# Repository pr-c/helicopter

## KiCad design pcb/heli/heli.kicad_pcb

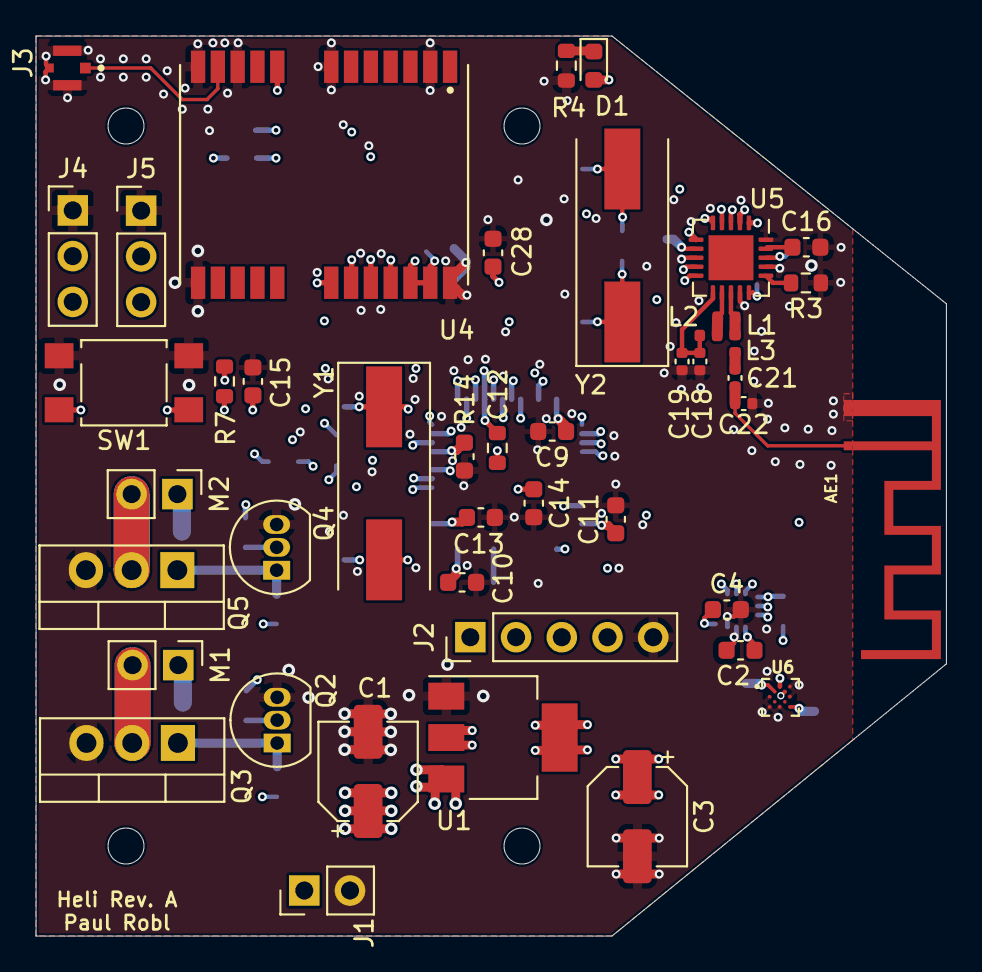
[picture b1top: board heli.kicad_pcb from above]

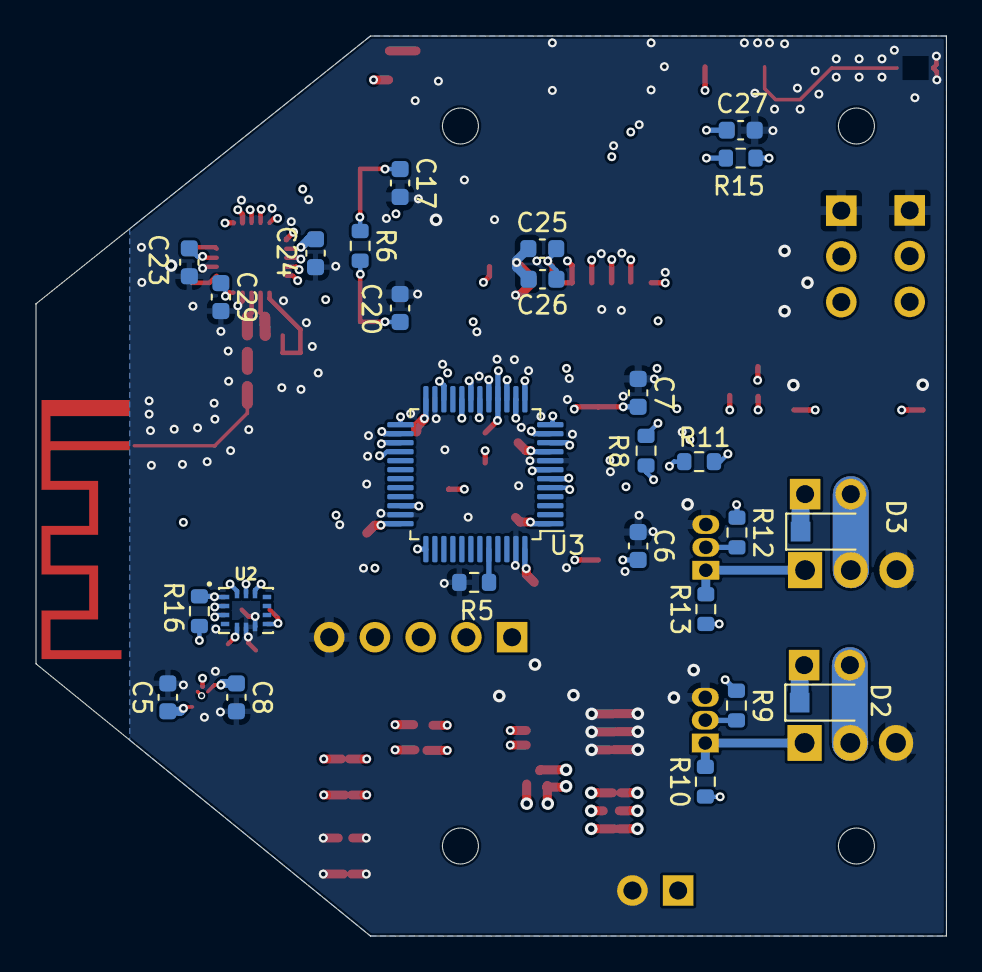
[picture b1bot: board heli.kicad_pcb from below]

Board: 4 copper layers, 50.6 x 50.0 mm, 72 parts (26 on the bottom side), 44 nets.

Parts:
**REF: MountingHole_2mm
**REF#2: MountingHole_2mm
AE1: Antenna_Shield; TRACE_ANTENNA_2.4GHZ_15.2MM
C1: 10uF; CP_Elec_5x5.4
C2, C4, C5, C8, C9, C10, C11, C12, C13, C15, C25, C26, C27, C29: 100nF; C_0603_1608Metric
C3: 22uF; CP_Elec_5x5.4
C6, C7, C17, C20: 30pF; C_0603_1608Metric
C14, C28: 10uF; C_0603_1608Metric
C16: 33nF; C_0603_1608Metric
C18: 2.2nF; C_0402_1005Metric
C19: 4.7pF; C_0402_1005Metric
C21: 1.5pF; C_0402_1005Metric
C22: 1.0pF; C_0402_1005Metric
C23: 10nF; C_0603_1608Metric
C24: 1nF; C_0603_1608Metric
D1: LED; LED_0603_1608Metric
D2, D3: 1N5819; D_SOD-123F
J1: Batterie; PinHeader_1x02_P2.54mm_Vertical
J2: Debug; PinHeader_1x05_P2.54mm_Vertical
J3: CONMHF4-SMD-G-T; LINX_CONMHF4-SMD-G-T
J4, J5: Servo; PinHeader_1x03_P2.54mm_Vertical
L1: 8.2nH; L_0402_1005Metric
L2: 2.7nH; L_0402_1005Metric
L3: 3.9nH; L_0402_1005Metric
M1, M2: Motor_DC; PinHeader_1x02_P2.54mm_Vertical
Q2, Q4: BC547; TO-92_Inline
Q3, Q5: IRLZ44N; TO-220-3_Vertical
R3: 22k; R_0603_1608Metric
R4: 70; R_0603_1608Metric
R5, R7, R10, R13, R15: 10k; R_0603_1608Metric
R6, R8, R11, R14, R16: 1M; R_0603_1608Metric
R9, R12: 20k; R_0603_1608Metric
SW1: SW_MEC_5E; SW_SPST_TL3305A
U1: AZ1117-3.3; SOT-223-3_TabPin2
U2: BMI270; XDCR_BMI270
U3: STM32F103CBTx; LQFP-48_7x7mm_P0.5mm
U4: NEO-M9N-00B; XCVR_NEO-M9N-00B
U5: NRF24L01; QFN-20-1EP_4x4mm_P0.5mm_EP2.5x2.5mm
U6: BMM150; XDCR_BMM150
Y1: 8MHz; Crystal_SMD_HC49-SD
Y2: 16MHz; Crystal_SMD_HC49-SD

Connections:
3.3V: C2.1, C3.1, C4.1, C5.1, C8.1, C9.1, C10.1, C11.1, C12.1, C13.1, C14.1, C23.1, C24.1, C25.1, C26.1, C28.1, C29.1, D1.2 (A), J2.1, J4.2, J5.2, R7.1, R8.1, R11.1, R14.1, R15.1, R16.1, U1.2 (VO), U2.5 (VDDIO), U2.8 (VDD), U3.1 (VBAT), U3.9 (VDDA), U3.24 (VDD), U3.36 (VDD), U3.48 (VDD), U4.22 (V_BCKP), U4.23 (VCC), U5.7 (VDD), U5.15 (VDD), U5.18 (VDD), U6.A1 (PS), U6.B2 (VDDIO), U6.E5 (VDD)
7.4V: C1.1, D2.1 (K), D3.1 (K), J1.1, M1.1 (+), M2.1 (+), R10.1, R13.1, U1.3 (VI)
/Back Motor/M-: D3.2 (A), M2.2 (-), Q5.2 (D)
/GPS/GPS50ohms: J3.1, U4.11 (RF_IN)
/IMU/SCL: U2.3 (ASCX), U6.A3 (SCK)
/IMU/SDA: U2.2 (ASDX), U6.B4 (SDI)
/Main Motor/M-: D2.2 (A), M1.2 (-), Q3.2 (D)
/PWM1: R8.2, R9.1, U3.10 (PA0)
/PWM2: R11.2, R12.1, U3.11 (PA1)
/Radio/RADIO50ohm: AE1.1 (A), C21.2, C22.2
/SERVO1: J4.3, U3.12 (PA2)
/SERVO2: J5.3, U3.13 (PA3)
GND: AE1.2 (Shield), C1.2, C2.2, C3.2, C4.2, C5.2, C6.1, C7.1, C8.2, C9.2, C10.2, C11.2, C12.2, C13.2, C14.2, C15.1, C16.2, C17.2, C18.1, C19.1, C20.2, C22.1, C23.2, C24.2, C25.2, C26.2, C27.1, C28.2, C29.2, J1.2, J2.5, J3.S1, J3.S2, J3.S3, J4.1, J5.1, Q2.3 (E), Q3.3 (S), Q4.3 (E), Q5.3 (S), R3.1, R4.2, R5.1, SW1.2, U1.1 (GND), U2.6 (GNDIO), U2.7 (GND), U3.8 (VSSA), U3.23 (VSS), U3.35 (VSS), U3.47 (VSS), U4.2 (D_SEL), U4.7 (V_USB), U4.10 (GND), U4.12 (GND), U4.13 (GND), U4.24 (GND), U5.8 (VSS), U5.14 (VSS), U5.17 (VSS), U5.20 (VSS), U6.A5 (CSB), U6.C1 (SDO), U6.C5 (GND), U6.E1 (GND), U6.E3 (GND)
GPS_CSN: U3.22 (PB11), U4.18 (SDA/SPI_CS_N)
GPS_NRST: C27.2, R15.2, U3.14 (PA4), U4.8 (RESET_N)
IMU_CSN: U2.12 (CSB), U3.25 (PB12)
unnamed: C6.2, U3.5 (PD0), Y1.2
unnamed: C7.2, U3.6 (PD1), Y1.1
unnamed: C16.1, U5.19 (DVDD)
unnamed: C17.1, R6.1, U5.9 (XC2), Y2.2
unnamed: C18.2, C19.2, L2.2, U5.11 (VDD_PA)
unnamed: C20.1, R6.2, U5.10 (XC1), Y2.1
unnamed: C21.1, L3.2
unnamed: D1.1 (K), R4.1
unnamed: L1.1, L2.1, U5.12 (ANT1)
unnamed: L1.2, L3.1, U5.13 (ANT2)
unnamed: Q2.1 (C), Q3.1 (G), R10.2
unnamed: Q2.2 (B), R9.2
unnamed: Q4.1 (C), Q5.1 (G), R13.2
unnamed: Q4.2 (B), R12.2
unnamed: R3.2, U5.16 (IREF)
unnamed: R5.2, U3.44 (BOOT0)
RADIO_CE: U3.18 (PB0), U5.1 (CE)
RADIO_CSN: U3.19 (PB1), U5.2 (CSN)
RADIO_IRQ: U3.20 (PB2), U5.6 (IRQ)
RESET: C15.2, J2.4, R7.2, SW1.1, U3.7 (NRST)
SPI2_MISO: R16.2, U2.1 (SDO), U3.27 (PB14)
SPI2_MOSI: U2.14 (SDX), U3.28 (PB15)
SPI2_SCK: U2.13 (SCX), U3.26 (PB13)
SPI_MISO: R14.2, U3.16 (PA6), U4.20 (TXD/SPI_MISO), U5.5 (MISO)
SPI_MOSI: U3.17 (PA7), U4.21 (RXD/SPI_MOSI), U5.4 (MOSI)
SPI_SCK: U3.15 (PA5), U4.19 (SCL/SPI_CLK), U5.3 (SCK)
SWCLK: J2.2, U3.37 (PA14)
SWDIO: J2.3, U3.34 (PA13)

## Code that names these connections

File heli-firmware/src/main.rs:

//! Testing PWM output for pre-defined pin combination: all pins for default mapping

#![deny(unsafe_code)]
#![allow(clippy::empty_loop)]
#![allow(clippy::approx_constant)]
#![no_main]
#![no_std]

use panic_halt as _;
use cortex_m_rt::entry;
use cortex_m_semihosting::hprintln;
use stm32f1xx_hal::afio::AfioExt;
use stm32f1xx_hal::flash::FlashExt;
use stm32f1xx_hal::gpio::GpioExt;
use stm32f1xx_hal::i2c::{BlockingI2c, DutyCycle};
use stm32f1xx_hal::{i2c, pac, spi};
use stm32f1xx_hal::prelude::{_embedded_hal_blocking_spi_Write, _fugit_RateExtU32};
use stm32f1xx_hal::rcc::RccExt;
use mpu6050_dmp::{sensor::Mpu6050, address::Address};
use mpu6050_dmp::euler::Euler;
use mpu6050_dmp::quaternion::Quaternion;
use stm32f1xx_hal::spi::{Phase, Polarity, Spi};
use stm32f1xx_hal::timer::{Channel, SysTimerExt, Tim2NoRemap, Timer};
use embedded_nrf24l01::{NRF24L01, Configuration, DataRate, CrcMode};

const PI: f32 = 3.1415927;
const PI2_INVERTED: f32 = 1.0 / (2.0 * PI);

const SPI_MODE: spi::Mode = spi::Mode {
    phase: Phase::CaptureOnFirstTransition,
    polarity: Polarity::IdleLow,
};

#[entry]
fn main() -> ! {
    hprintln!("Startup...");
    let core_peripherals = cortex_m::Peripherals::take().unwrap();
    let device_peripherals = pac::Peripherals::take().unwrap();

    let mut flash = device_peripherals.FLASH.constrain();
    let rcc = device_peripherals.RCC.constrain();
    let mut afio = device_peripherals.AFIO.constrain();

    let clock = rcc.cfgr.use_hse(8.MHz()).sysclk(48.MHz()).pclk1(6.MHz()).freeze(&mut flash.acr);

    let mut gpioa = device_peripherals.GPIOA.split();
    let mut gpiob = device_peripherals.GPIOB.split();

    let scl = gpiob.pb6.into_alternate_open_drain(&mut gpiob.crl);
    let sda = gpiob.pb7.into_alternate_open_drain(&mut gpiob.crl);

    let pwm_pin_pa0 = gpioa.pa0.into_alternate_push_pull(&mut gpioa.crl);
    let pwm_pin_pa1 = gpioa.pa1.into_alternate_push_pull(&mut gpioa.crl);

    let spi_sck_pin = gpioa.pa5.into_alternate_push_pull(&mut gpioa.crl);
    let spi_miso_pin = gpioa.pa6;
    let spi_mosi_pin = gpioa.pa7.into_alternate_push_pull(&mut gpioa.crl);
    let spi_cs_pin = gpioa.pa8.into_push_pull_output(&mut gpioa.crh);

    let ce_pin = gpioa.pa9.into_push_pull_output(&mut gpioa.crh);

    let mut spi = Spi::spi1(device_peripherals.SPI1, (spi_sck_pin, spi_miso_pin, spi_mosi_pin), &mut afio.mapr, SPI_MODE, 1.MHz(), clock);

    let mut pwm = Timer::new(device_peripherals.TIM2, &clock).pwm_hz::<Tim2NoRemap, _, _>((pwm_pin_pa0, pwm_pin_pa1), &mut afio.mapr, 1.kHz());
    pwm.enable(Channel::C1);
    pwm.enable(Channel::C2);
    pwm.set_period(50.kHz());
    let max = pwm.get_max_duty();

    let (mut pwm1, mut pwm2) = pwm.split();
    pwm1.set_duty(max / 2);
    pwm2.set_duty(max / 4);

    let i2c = BlockingI2c::i2c1(
        device_peripherals.I2C1,
        (scl, sda),
        &mut afio.mapr,
        i2c::Mode::Fast {
            frequency: 400.kHz(),
            duty_cycle: DutyCycle::Ratio16to9,
        },
        clock,
        1000,
        10,
        1000,
        1000,
    );
    hprintln!("Pins configured.");


    let mut sensor = Mpu6050::new(i2c, Address::default()).unwrap();

    hprintln!("Sensor object created.");
    let mut delay = core_peripherals.SYST.delay(&clock);
    sensor.initialize_dmp(&mut delay).unwrap();
    sensor.enable_dmp().unwrap();
    hprintln!("Sensor configured.");

    spi.write("test".as_bytes()).unwrap();
    hprintln!("SPI WRIITTEN");

    let nrf24_result = NRF24L01::new(ce_pin, spi_cs_pin, spi);
    hprintln!("NO PANIC DIGGA");
    let nrf24 = nrf24_result.unwrap();
    hprintln!("Transceiver object created.");
    let mut nrf24_rx = nrf24.rx().unwrap();
    nrf24_rx.set_frequency(0).unwrap();
    nrf24_rx.set_rf(&DataRate::R2Mbps, 0).unwrap();
    nrf24_rx.set_crc(CrcMode::TwoBytes).unwrap();

    hprintln!("---- Initialized ----");


    loop {
        let len = sensor.get_fifo_count().unwrap();
        if len >= 28 {
            let mut b: [u8; 28] = [0; 28];
            let buf = sensor.read_fifo(&mut b).unwrap();
            let q = Quaternion::from_bytes(&buf[..16]).unwrap().normalize();
            let euler = Euler::from(q);

            let a = (euler.phi as f32 + PI) * PI2_INVERTED * max as f32;
            let b = (euler.psi as f32 + PI) * PI2_INVERTED * max as f32;
            pwm1.set_duty(a as u16);
            pwm2.set_duty(b as u16);
        }
    }
}

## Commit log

2022-12-27 Added BMI270 to schematic and SPI2 to the code
2022-12-27 Removed MPU6050, updated pcb
2022-12-27 Added BMM150 as BMI270 i2c slave
2022-12-28 Silk screen cleaned up
2022-12-28 Manufacturing Candidate
